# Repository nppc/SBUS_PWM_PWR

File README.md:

# SBUS to PWM converter with power switch

Mini board for an 1m DLG to control 4 PWM servos from SBUS receiver.

Additinal functionality included power switch (reed switch or button) and connection for boost DC/DC to get 5V from 1S battery.

In standby mode the board consumes only 0.3uA. It means that on 200mA battery the board can stay in standby more than 50 years.

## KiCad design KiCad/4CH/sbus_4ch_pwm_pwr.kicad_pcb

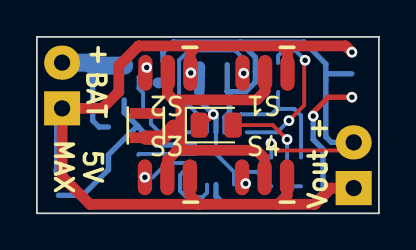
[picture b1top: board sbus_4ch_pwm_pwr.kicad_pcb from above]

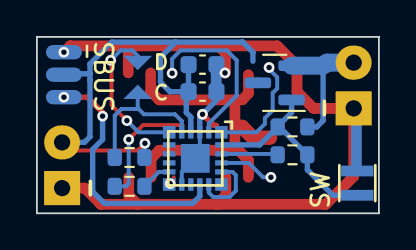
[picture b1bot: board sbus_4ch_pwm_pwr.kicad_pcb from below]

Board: 2 copper layers, 19.0 x 9.8 mm, 20 parts (12 on the bottom side), 16 nets.

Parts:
C1: 100n; C_0603_1608Metric
C2: 10uf; C_0603_1608Metric
D1: LED; LED_0805_2012Metric
J1: S2; Pads_prog_3pin1.25mm
J2: S1; Pads_prog_3pin1.25mm
J3: S3; Pads_prog_3pin1.25mm
J4: S4; Pads_prog_3pin1.25mm
J5: SBUS; Pads_prog_3pin1.25mm
J6: C2CK; RC_PAD_TRIANGLE
J7: C2D; RC_PAD_TRIANGLE
J8: BAT; Conn_1x02_2.54_0.9mm
J9: DC/DC; XFL2006-inductor
J10: SW; XFL2006-inductor
J11: PWR; Conn_1x02_2.54_0.9mm
Q1: AO3415; SOT-23
R1, R3: 4.7K; R_0603_1608Metric
R2: 100K; R_0603_1608Metric
R4: 560; R_0603_1608Metric
U1: EFM8BB51; QFN20

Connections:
+BATT: J8.2, Q1.2 (S), R2.1
/BUT_SENS: J10.2, Q1.1 (G), R2.2, R3.1, U1.20 (P0.2)
/C2CK: J6.1, R1.2, U1.5 (RSTb/C2CK)
/C2D: J7.1, U1.6 (P2.0/C2D)
/LED: R4.1, U1.10 (P1.3)
/MOSFET: R3.2, U1.19 (P0.3)
/PWM1: J2.3, U1.2 (P0.0)
/PWM2: J1.3, U1.1 (P0.1)
/PWM3: J3.3, U1.18 (P0.4)
/PWM4: J4.3, U1.11 (P1.2)
/SBUS: J5.3, U1.14 (P1.0)
GND: C1.2, C2.2, D1.1 (K), J1.1, J2.1, J3.1, J4.1, J5.1, J8.1, J10.1, J11.1, U1.3 (GND), U1.12 (GND), U1.21 (GND)
unnamed: D1.2 (A), R4.2
unnamed: U1.15 (P0.7), U1.17 (P0.5)
VBUS: C1.1, C2.1, J1.2, J2.2, J3.2, J4.2, J5.2, J9.2, J11.2, R1.1, U1.4 (VDD)
VDD: J9.1, Q1.3 (D)

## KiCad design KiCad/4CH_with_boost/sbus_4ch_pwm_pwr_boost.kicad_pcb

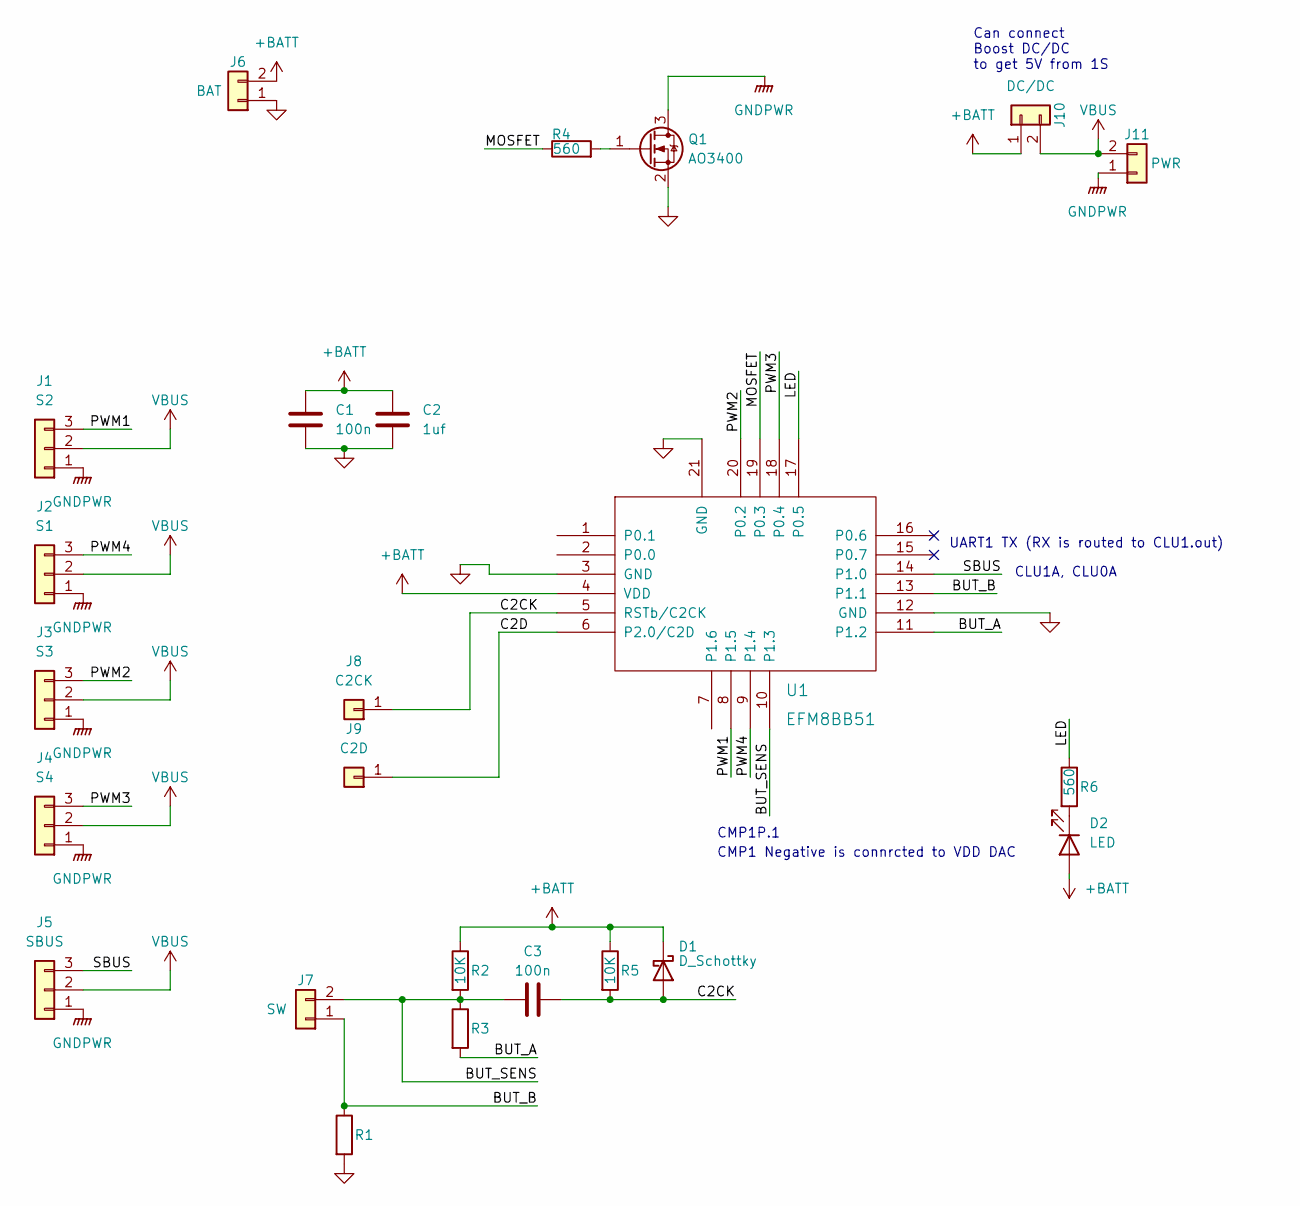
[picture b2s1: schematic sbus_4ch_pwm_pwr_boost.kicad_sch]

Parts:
C1, C3: 100n; C_0603_1608Metric
C2: 1uf; C_0603_1608Metric
D1: D_Schottky; D_SOD-523
D2: LED; LED_0805_2012Metric
J1: S2; Pads_prog_3pin1.25mm
J2: S1; Pads_prog_3pin1.25mm
J3: S3; Pads_prog_3pin1.25mm
J4: S4; Pads_prog_3pin1.25mm
J5: SBUS; Pads_prog_3pin1.25mm
J6: BAT; Conn_1x02_2.54_0.9mm
J7: SW; XFL2006-inductor
J8: C2CK; RC_PAD_TRIANGLE
J9: C2D; RC_PAD_TRIANGLE
J10: DC/DC; XFL2006-inductor
J11: PWR; PinHeader_1x02_P2.00mm_Vertical
Q1: AO3400; SOT-23
R1, R3: R_0603_1608Metric
R2, R5: 10K; R_0603_1608Metric
R4, R6: 560; R_0603_1608Metric
U1: EFM8BB51; QFN20

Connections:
+BATT: C1.1, C2.1, D1.1 (K), D2.2 (A), J6.2, J10.1, R2.1, R5.1, U1.4 (VDD)
/BUT_A: R3.2, U1.11 (P1.2)
/BUT_B: J7.1, R1.1, U1.13 (P1.1)
/BUT_SENS: C3.1, J7.2, R2.2, R3.1, U1.10 (P1.3)
/C2CK: C3.2, D1.2 (A), J8.1, R5.2, U1.5 (RSTb/C2CK)
/C2D: J9.1, U1.6 (P2.0/C2D)
/LED: R6.1, U1.17 (P0.5)
/MOSFET: R4.1, U1.19 (P0.3)
/PWM1: J1.3, U1.8 (P1.5)
/PWM2: J3.3, U1.20 (P0.2)
/PWM3: J4.3, U1.18 (P0.4)
/PWM4: J2.3, U1.9 (P1.4)
/SBUS: J5.3, U1.14 (P1.0)
GND: C1.2, C2.2, J6.1, Q1.2 (S), R1.2, U1.3 (GND), U1.12 (GND), U1.21 (GND)
GNDPWR: J1.1, J2.1, J3.1, J4.1, J5.1, J11.1, Q1.3 (D)
unnamed: D2.1 (K), R6.2
unnamed: Q1.1 (G), R4.2
VBUS: J1.2, J2.2, J3.2, J4.2, J5.2, J10.2, J11.2

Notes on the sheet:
UART1 TX (RX is routed to CLU1.out)
CMP1 Negative is connrcted to VDD DAC
Can connect Boost DC/DC to get 5V from 1S
CMP1P.1
CLU1A, CLU0A

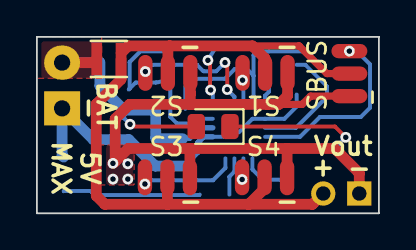
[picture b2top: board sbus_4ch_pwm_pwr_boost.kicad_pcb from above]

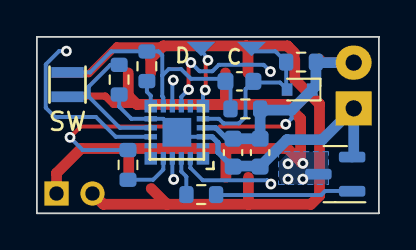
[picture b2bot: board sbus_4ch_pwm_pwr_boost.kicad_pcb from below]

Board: 2 copper layers, 19.0 x 9.8 mm, 24 parts (16 on the bottom side), 18 nets.

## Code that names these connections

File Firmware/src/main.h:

#include <SI_EFM8BB51_Register_Enums.h>                  // SFR declarations
#include <SI_EFM8BB51_Defs.h>
#include <stdint.h>

#ifndef MAIN_H_
#define MAIN_H_


// Structure for accessing 16bit number by 2 8 bit (back and forth)
// Usage:
// U16_U8 ptr;
// ptr.u8[0] = high;
// ptr.u8[1] = low;
// ptr.u16 = 16bit;
typedef union
   {
   unsigned short u16;
   unsigned char u8[2];
   } U16_U8;

extern void waitNms(uint16_t ms);
extern uint16_t convert_sbus_2_pwm(uint16_t val);
extern void goPowerDown(void);
extern bit isVoltageLow(void);

//SI_SBIT(PIN_PWM1, SFR_P1, 5); // TSSOP-20 PIN10
//SI_SBIT(PIN_PWM2, SFR_P0, 2); // TSSOP-20 PIN2
//SI_SBIT(PIN_PWM3, SFR_P0, 4); // TSSOP-20 PIN20
//SI_SBIT(PIN_PWM4, SFR_P1, 4); // TSSOP-20 PIN11
//SI_SBIT(PIN_SBUS, SFR_P1, 0); // TSSOP-20 PIN16
SI_SBIT(PIN_LED, SFR_P0, 5);  // TSSOP-20 PIN19
SI_SBIT(PIN_MOSFET, SFR_P0, 3); // TSSOP-20 PIN1
SI_SBIT(PIN_BUTA, SFR_P1, 2); // TSSOP-20 PIN13
SI_SBIT(PIN_BUTB, SFR_P1, 1); // TSSOP-20 PIN15
SI_SBIT(PIN_BUT_SENS, SFR_P1, 3); // TSSOP-20 PIN12
// CLU1A TSSOP-20 PIN 16


extern U16_U8 pwm_channels[];
extern bit PWM_started;
extern uint8_t delay_powering_counter;
extern uint8_t led_pattern, led_pattern_counter;
extern uint16_t timeout_counter;
extern bit timeout_tick;

#endif /* MAIN_H_ */

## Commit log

2023-11-07 Add working version of the board
